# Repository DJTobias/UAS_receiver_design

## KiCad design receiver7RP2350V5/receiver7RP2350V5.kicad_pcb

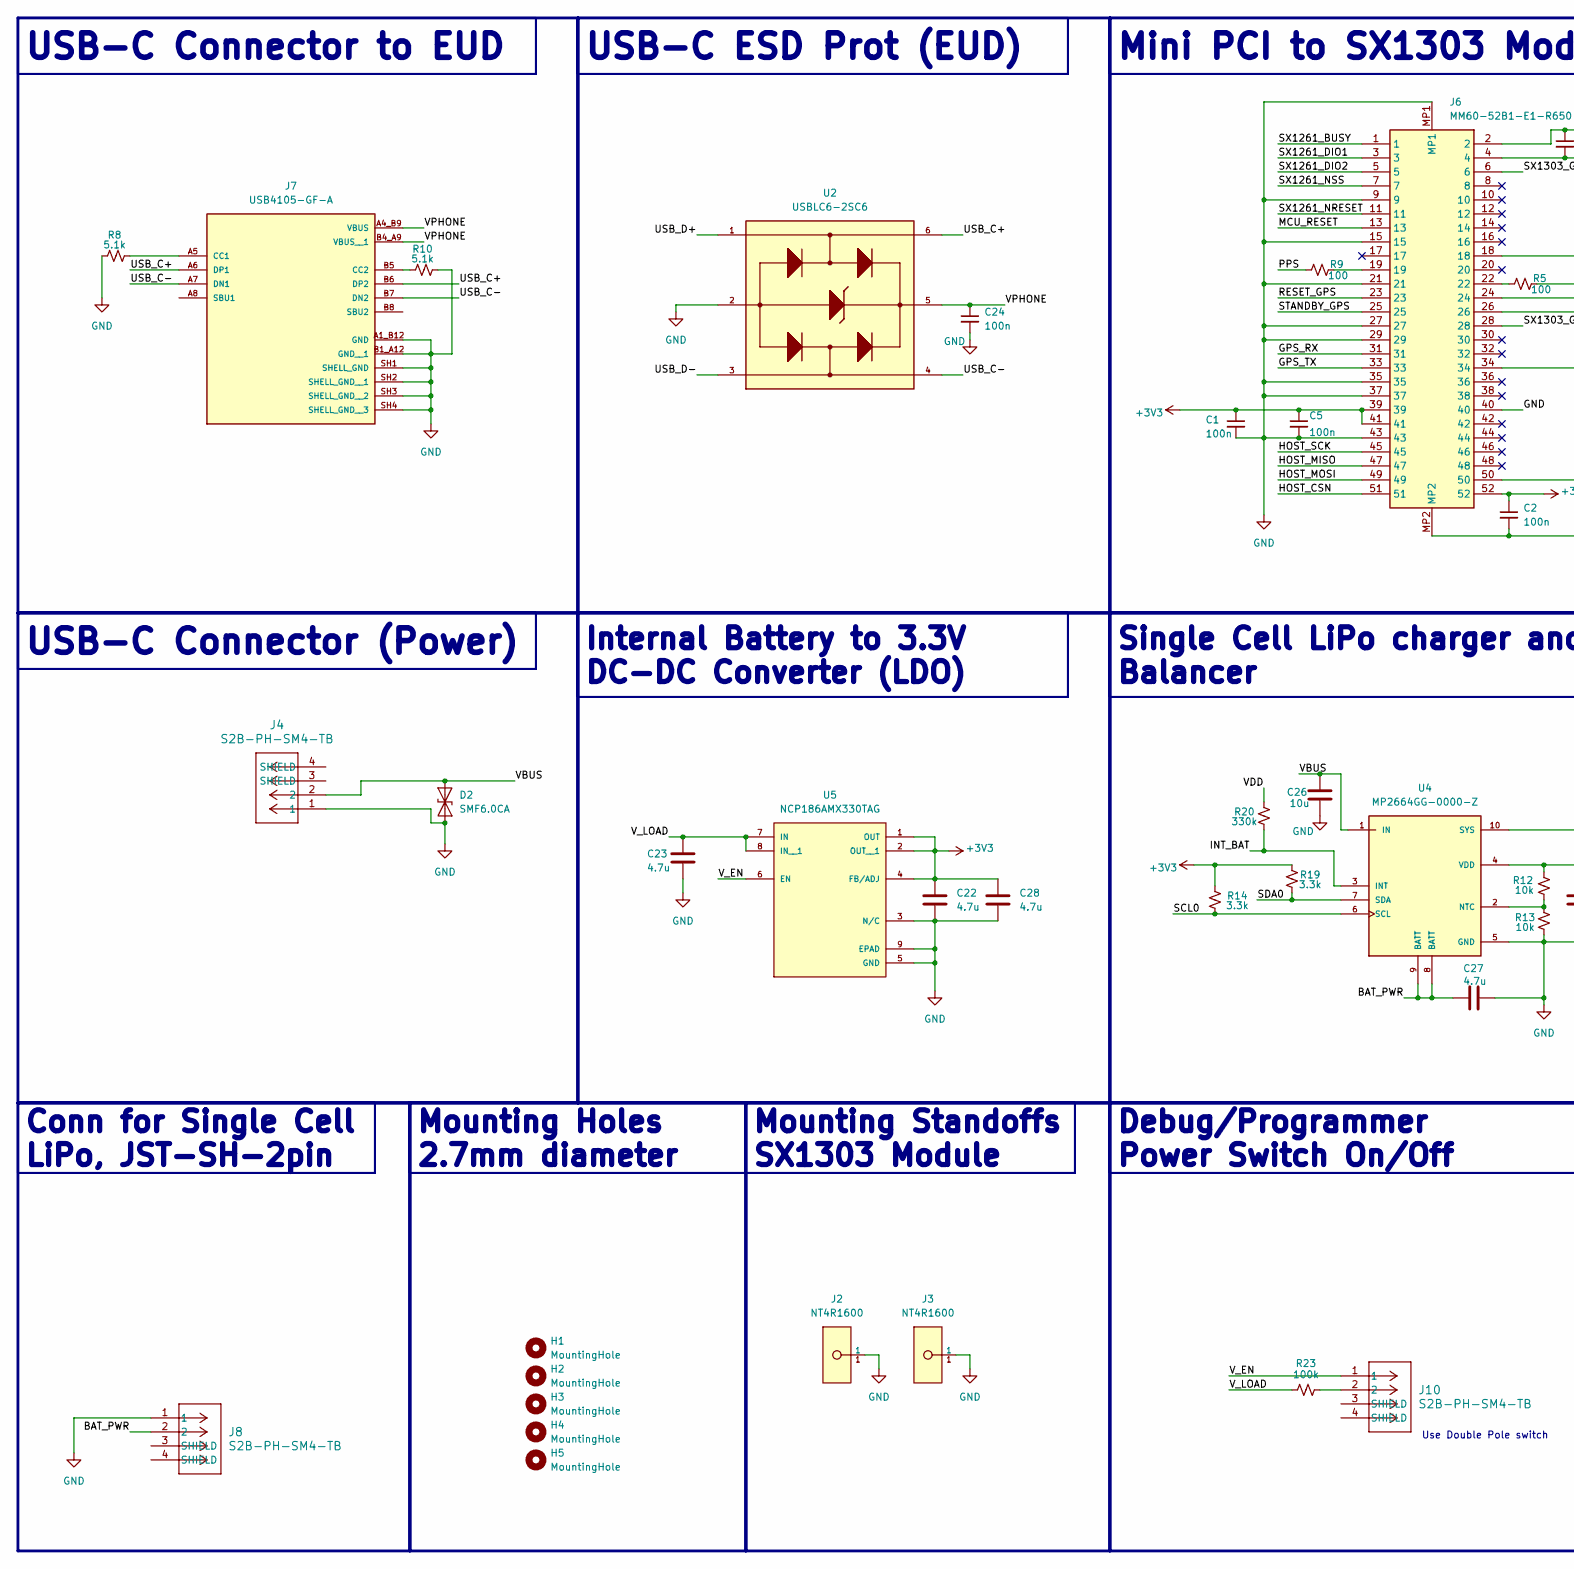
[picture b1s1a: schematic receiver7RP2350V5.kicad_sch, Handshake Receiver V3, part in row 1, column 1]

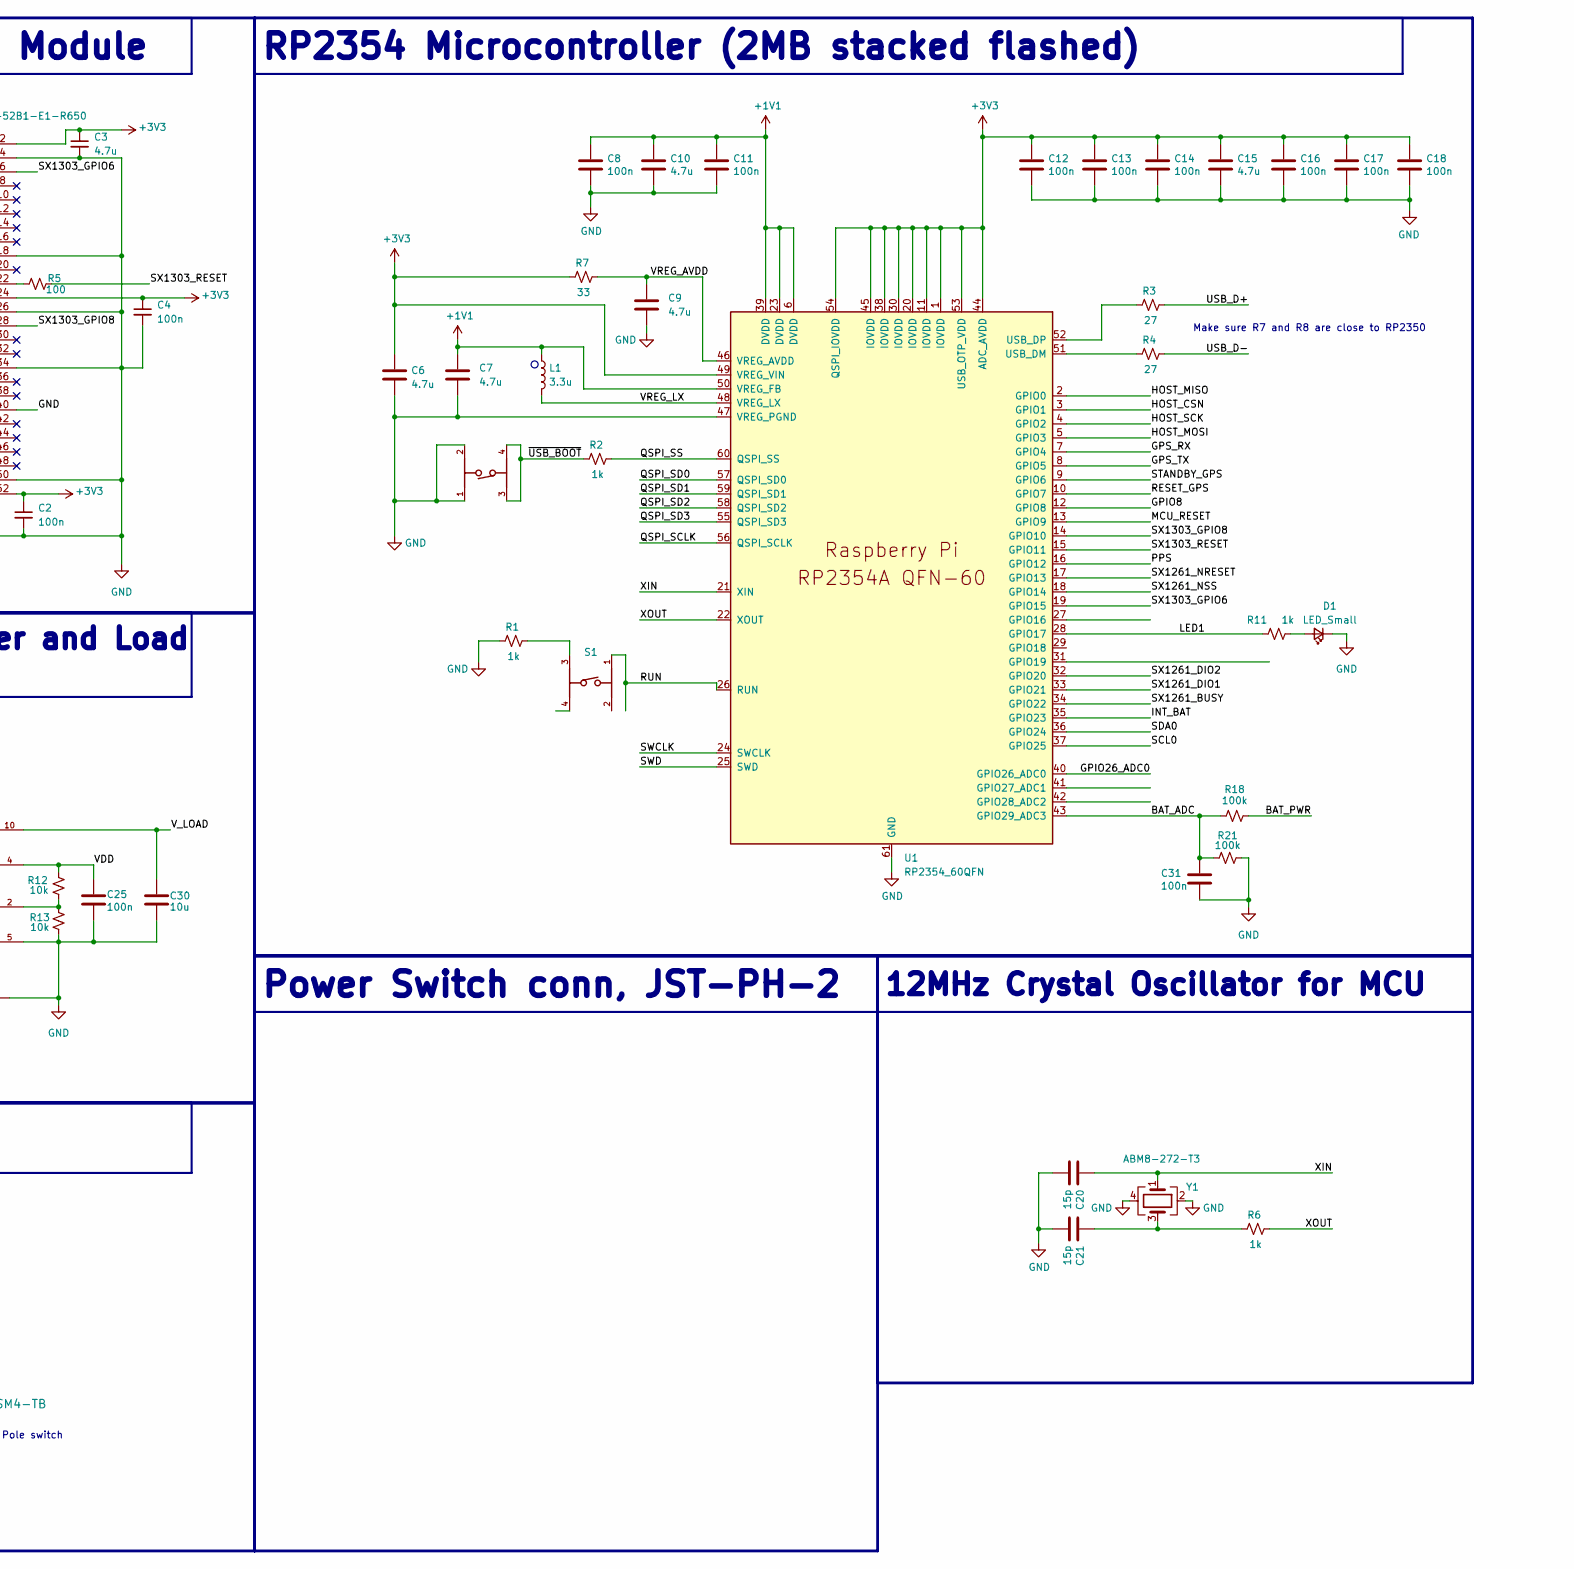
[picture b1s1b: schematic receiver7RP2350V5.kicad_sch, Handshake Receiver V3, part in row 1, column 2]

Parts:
C1, C2, C4, C5, C8, C11, C12, C13, C14, C16, C17, C18, C24, C25, C31: 100n; C_0402_1005Metric
C3, C9, C10, C15, C22, C23, C27, C28: 4.7u; C_0402_1005Metric
C6, C7: 4.7u; C_0402_1005Metric_small_pads
C20, C21: 15p; C_0402_1005Metric
C26, C30: 10u; C_0805_2012Metric
D1: LED_Small; LED_0402_1005Metric
D2: SMF6.0CA; SMF26CA_Custom
H1: MountingHole; MountingHole_2.5mm
H2, H3, H4, H5: MountingHole; MountingHole_2.7mm_M2.5_Pad_Via
J2, J3: NT4R1600; JAE_Electronics-NT4R1600-MFG; mouser part number 656-NT4R1600; digikey description STANDOFF FOR MM60 SERIES
J4, J8, J10: S2B-PH-SM4-TB; CONN_S2B-PH-SM4-TB_JST_mod2
J6: MM60-52B1-E1-R650; MM6052B1E1R650_mod_screw; Mouser Part Number 656-MM60-52B1-E1-R
J7: USB4105-GF-A; GCT_USB4105-GF-A; PARTREV B4
L1: 3.3u; L_pol_2016
R1, R2, R6, R11: 1k; R_0402_1005Metric
R3, R4: 27; R_0402_1005Metric
R5, R9: 100; R_0402_1005Metric
R7: 33; R_0402_1005Metric
R8, R10: 5.1k; R_0402_1005Metric
R12, R13: 10k; R_0402_1005Metric
R14, R19: 3.3k; R_0402_1005Metric
R18, R21, R23: 100k; R_0402_1005Metric
R20: 330k; R_0402_1005Metric
S1, S2: 434133025816; 434133025816_mod
U1: RP2354_60QFN; RP2350-QFN-60-1EP_7x7_P0.4mm_EP3.4x3.4mm_ThermalVias
U2: USBLC6-2SC6; SOT95P280X145-6N
U4: MP2664GG-0000-Z; QFN50P200X200X105-10N; PARTREV 1.01
U5: NCP186AMX330TAG; PSON40P160X120X45-9N; PARTREV Rev.5
Y1: ABM8-272-T3; Crystal_SMD_3225-4Pin_3.2x2.5mm

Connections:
+1V1: C7.1, C8.1, C10.1, C11.1, L1.1, U1.6 (DVDD), U1.23 (DVDD), U1.39 (DVDD), U1.50 (VREG_FB)
+3V3: C1.1, C2.1, C3.1, C4.1, C5.1, C6.1, C12.1, C13.1, C14.1, C15.1, C16.1, C17.1, C18.1, C22.1, C28.1, J6.2, J6.24, J6.39, J6.41, J6.52, R7.1, R14.2, R19.2, U1.1 (IOVDD), U1.11 (IOVDD), U1.20 (IOVDD), U1.30 (IOVDD), U1.38 (IOVDD), U1.44 (ADC_AVDD), U1.45 (IOVDD), U1.49 (VREG_VIN), U1.53 (USB_OTP_VDD), U1.54 (QSPI_IOVDD), U5.1 (OUT), U5.2 (OUT__1), U5.4 (FB/ADJ)
/BAT_ADC: C31.1, R18.2, R21.2, U1.43 (GPIO29_ADC3)
/BAT_PWR: C27.1, J8.2, R18.1, U4.8 (BATT), U4.9 (BATT)
/GPIO8: U1.12 (GPIO8)
/GPIO26_ADC0: U1.40 (GPIO26_ADC0)
/GPS_RX: J6.31, U1.7 (GPIO4)
/GPS_TX: J6.33, U1.8 (GPIO5)
/HOST_CSN: J6.51, U1.3 (GPIO1)
/HOST_MISO: J6.47, U1.2 (GPIO0)
/HOST_MOSI: J6.49, U1.5 (GPIO3)
/HOST_SCK: J6.45, U1.4 (GPIO2)
/INT_BAT: R20.1, U1.35 (GPIO23), U4.3 (INT)
/LED1: R11.1, U1.28 (GPIO17)
/MCU_RESET: J6.13, U1.13 (GPIO9)
/PPS: R9.1, U1.16 (GPIO12)
/QSPI_SCLK: U1.56 (QSPI_SCLK)
/QSPI_SD0: U1.57 (QSPI_SD0)
/QSPI_SD1: U1.59 (QSPI_SD1)
/QSPI_SD2: U1.58 (QSPI_SD2)
/QSPI_SD3: U1.55 (QSPI_SD3)
/QSPI_SS: R2.2, U1.60 (QSPI_SS)
/RESET_GPS: J6.23, U1.10 (GPIO7)
/RUN: S1.1, U1.26 (RUN)
/SCL0: R14.1, U1.37 (GPIO25), U4.6 (SCL)
/SDA0: R19.1, U1.36 (GPIO24), U4.7 (SDA)
/STANDBY_GPS: J6.25, U1.9 (GPIO6)
/SWCLK: U1.24 (SWCLK)
/SWD: U1.25 (SWD)
/SX1261_BUSY: J6.1, U1.34 (GPIO22)
/SX1261_DIO1: J6.3, U1.33 (GPIO21)
/SX1261_DIO2: J6.5, U1.32 (GPIO20)
/SX1261_NRESET: J6.11, U1.17 (GPIO13)
/SX1261_NSS: J6.7, U1.18 (GPIO14)
/SX1303_GPIO6: J6.6, U1.19 (GPIO15)
/SX1303_GPIO8: J6.28, U1.14 (GPIO10)
/SX1303_RESET: R5.2, U1.15 (GPIO11)
/USB_C+: J7.A6 (DP1), J7.B6 (DP2), U2.6
/USB_C-: J7.A7 (DN1), J7.B7 (DN2), U2.4
/USB_D+: R3.2, U2.1
/USB_D-: R4.2, U2.3
/VBUS: C26.1, D2.2 (A2), J4.2, U4.1 (IN)
/VDD: C25.1, R12.2, R20.2, U4.4 (VDD)
/VPHONE: C24.1, J7.A4_B9 (VBUS), J7.B4_A9 (VBUS__1), U2.5
/VREG_AVDD: C9.1, R7.2, U1.46 (VREG_AVDD)
/VREG_LX: L1.2, U1.48 (VREG_LX)
/V_EN: J10.1, U5.6 (EN)
/V_LOAD: C23.1, C30.1, R23.2, U4.10 (SYS), U5.7 (IN), U5.8 (IN__1)
/XIN: C20.1, U1.21 (XIN), Y1.1
/XOUT: R6.2, U1.22 (XOUT)
/~USB_BOOT: R2.1, S2.3, S2.4
GND: C1.2, C2.2, C3.2, C4.2, C5.2, C6.2, C7.2, C8.2, C9.2, C10.2, C11.2, C12.2, C13.2, C14.2, C15.2, C16.2, C17.2, C18.2, C20.2, C21.2, C22.2, C23.2, C24.2, C25.2, C26.2, C27.2, C28.2, C30.2, C31.2, D1.1 (K), D2.1 (A1), J2.1, J3.1, J4.1, J6.4, J6.9, J6.15, J6.18, J6.21, J6.26, J6.27, J6.29, J6.34, J6.35, J6.37, J6.40, J6.43, J6.50, J6.MP1, J6.MP2, J7.A1_B12 (GND), J7.B1_A12 (GND__1), J7.SH1 (SHELL_GND), J7.SH2 (SHELL_GND__1), J7.SH3 (SHELL_GND__2), J7.SH4 (SHELL_GND__3), J8.1, R1.1, R8.1, R10.2, R13.1, R21.1, S2.1, S2.2, U1.47 (VREG_PGND), U1.61 (GND), U2.2, U4.5 (GND), U5.3 (N/C), U5.5 (GND), U5.9 (EPAD), Y1.2, Y1.4
unnamed: C21.1, R6.1, Y1.3
unnamed: D1.2 (A), R11.2
unnamed: J6.19, R9.2
unnamed: J6.22, R5.1
unnamed: J7.A5 (CC1), R8.2
unnamed: J7.B5 (CC2), R10.1
unnamed: J10.2, R23.1
unnamed: R1.2, S1.3
unnamed: R4.1, U1.51 (USB_DM)
unnamed: R3.1, U1.52 (USB_DP)
unnamed: R12.1, R13.2, U4.2 (NTC)

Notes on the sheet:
Use Double Pole switch
Make sure R7 and R8 are close to RP2350
12MHz Crystal Oscillator for MCU
Debug/Programmer Power Switch On/Off
Conn for Single Cell LiPo, JST-SH-2pin
USB-C Connector (Power)
Power Switch conn, JST-PH-2
Mini PCI to SX1303 Module
USB-C ESD Prot (EUD)
Mounting Holes 2.7mm diameter
Single Cell LiPo charger and Load Balancer
Internal Battery to 3.3V DC-DC Converter (LDO)
Mounting Standoffs SX1303 Module
USB-C Connector to EUD
RP2354 Microcontroller (2MB stacked flashed)

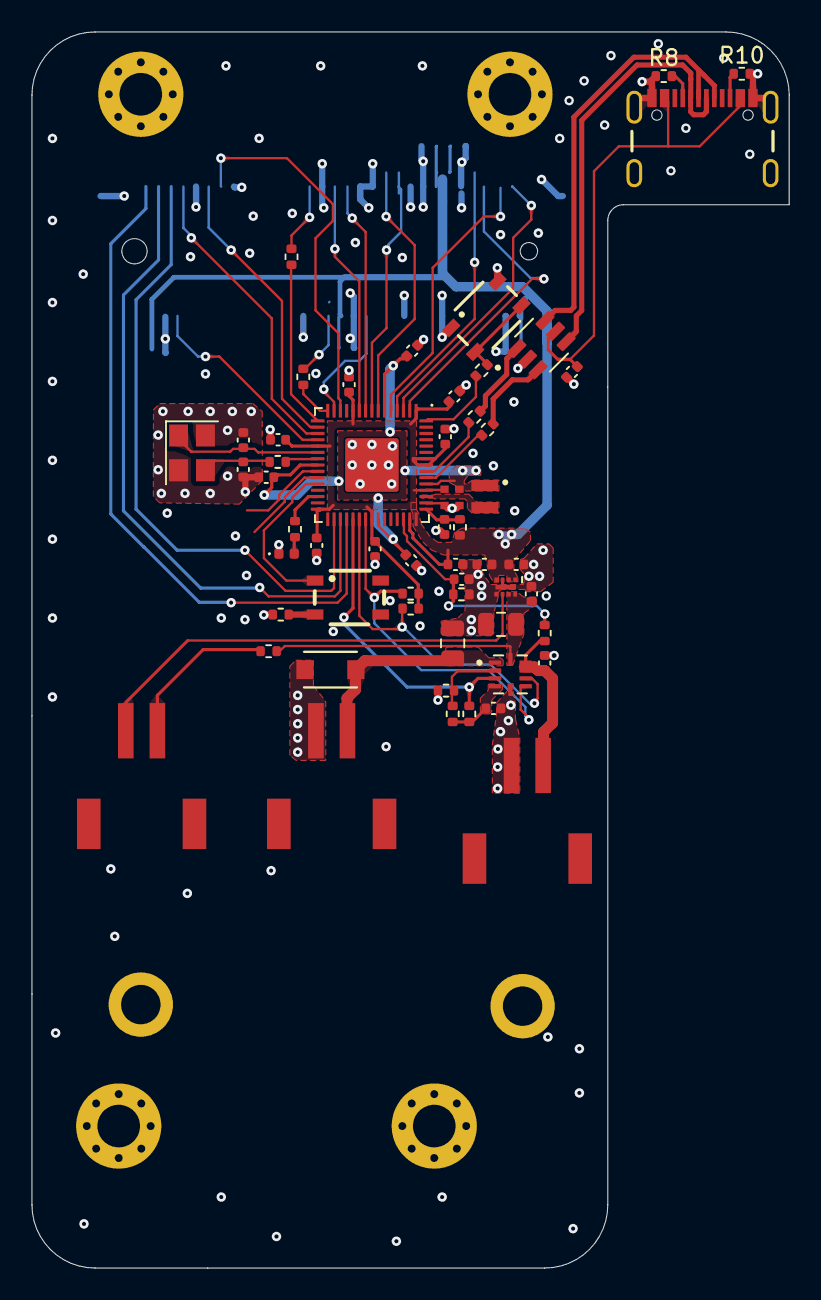
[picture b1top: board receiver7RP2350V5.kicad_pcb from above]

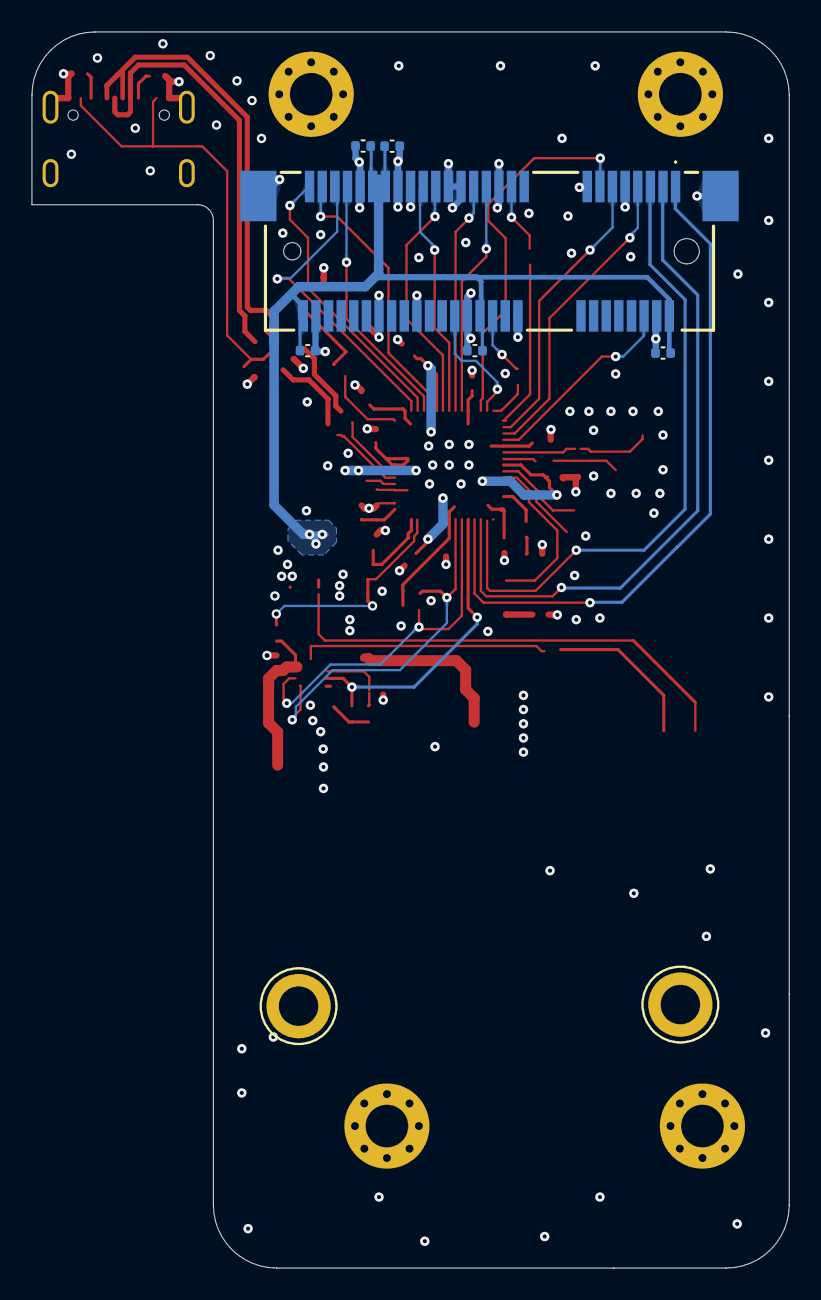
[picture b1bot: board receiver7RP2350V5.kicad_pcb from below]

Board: 4 copper layers, 48.0 x 78.3 mm, 70 parts (8 on the bottom side), 54 nets.

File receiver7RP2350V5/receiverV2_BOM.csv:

"Reference","Value","Datasheet","Footprint","Qty","DNP"
"C1,C2,C4,C5,C8,C11,C12,C13,C14,C16,C17,C18,C24,C25","100n","~","Capacitor_SMD:C_0402_1005Metric","14",""
"C3,C6,C7,C9,C10,C15,C27","4.7u","~","Capacitor_SMD:C_0402_1005Metric,RP2350_60QFN_minimal:C_0402_1005Metric_small_pads","7",""
"C19,C22,C23,C26,C30","10u","~","Capacitor_SMD:C_0805_2012Metric","5",""
"C20,C21","15p","~","Capacitor_SMD:C_0402_1005Metric","2",""
"D1","LED_Small","~","LED_SMD:LED_0402_1005Metric","1",""
"J1","BM04B-SRSS-TB","BM04B-SRSS-TB","BM04B_SRSS_TB:CONN4_BM04B-SRSS_JST","1",""
"J2,J3","NT4R1600","https://www.jae.com/en/connectors/series/detail/product/id=68912","NT4R1600:JAE_Electronics-NT4R1600-MFG","2",""
"J4","2pads","S3B-PH-SM4-TB","PADS:2pin pad_larger","1",""
"J6","MM60-52B1-E1-R650","https://www.mouser.in/datasheet/2/206/JAEIS03536_1-2550299.pdf","MM60-52B1-E1-R650:MM6052B1E1R650_mod_screw","1",""
"J7","USB4105-GF-A","","USB4105_GF_A:GCT_USB4105-GF-A","1",""
"J8,J10","S2B-PH-SM4-TB","S2B-PH-SM4-TB","JST2pin:CONN_S2B-PH-SM4-TB_JST_mod2","2",""
"L1","3.3u","~","RP2350_60QFN_minimal:L_pol_2016","1",""
"R1,R2,R6,R11","1k","~","Resistor_SMD:R_0402_1005Metric","4",""
"R3,R4","27","~","Resistor_SMD:R_0402_1005Metric","2",""
"R5,R9","100","~","Resistor_SMD:R_0402_1005Metric","2",""
"R7","33","~","Resistor_SMD:R_0402_1005Metric","1",""
"R8,R10","5.1k","~","Resistor_SMD:R_0402_1005Metric","2",""
"R12,R13","10k","~","Resistor_SMD:R_0402_1005Metric","2",""
"R14,R19","3.3k","~","Resistor_SMD:R_0402_1005Metric","2",""
"R15","100k","~","Resistor_SMD:R_0402_1005Metric","1",""
"R20","300k","~","Resistor_SMD:R_0402_1005Metric","1",""
"S1","434133025816","","434133025816:434133025816_mod","1",""
"U1","RP2350_60QFN","","RP2350_60QFN_minimal:RP2350-QFN-60-1EP_7x7_P0.4mm_EP3.4x3.4mm_ThermalVias","1",""
"U2","USBLC6-2SC6","","USBLC6_2SC6:SOT95P280X145-6N","1",""
"U3","AP7361C-33Y5-13","AP7361C-33Y5-13","AP7361C_33Y5_13:SOT89-5_DIO-M_MODGND","1",""
"U4","MP2664GG-0000-Z","","MP2664GG-0000-Z:QFN50P200X200X105-10N","1",""
"Y1","ABM8-272-T3","~","adafruit:Crystal_SMD_3225-4Pin_3.2x2.5mm","1",""

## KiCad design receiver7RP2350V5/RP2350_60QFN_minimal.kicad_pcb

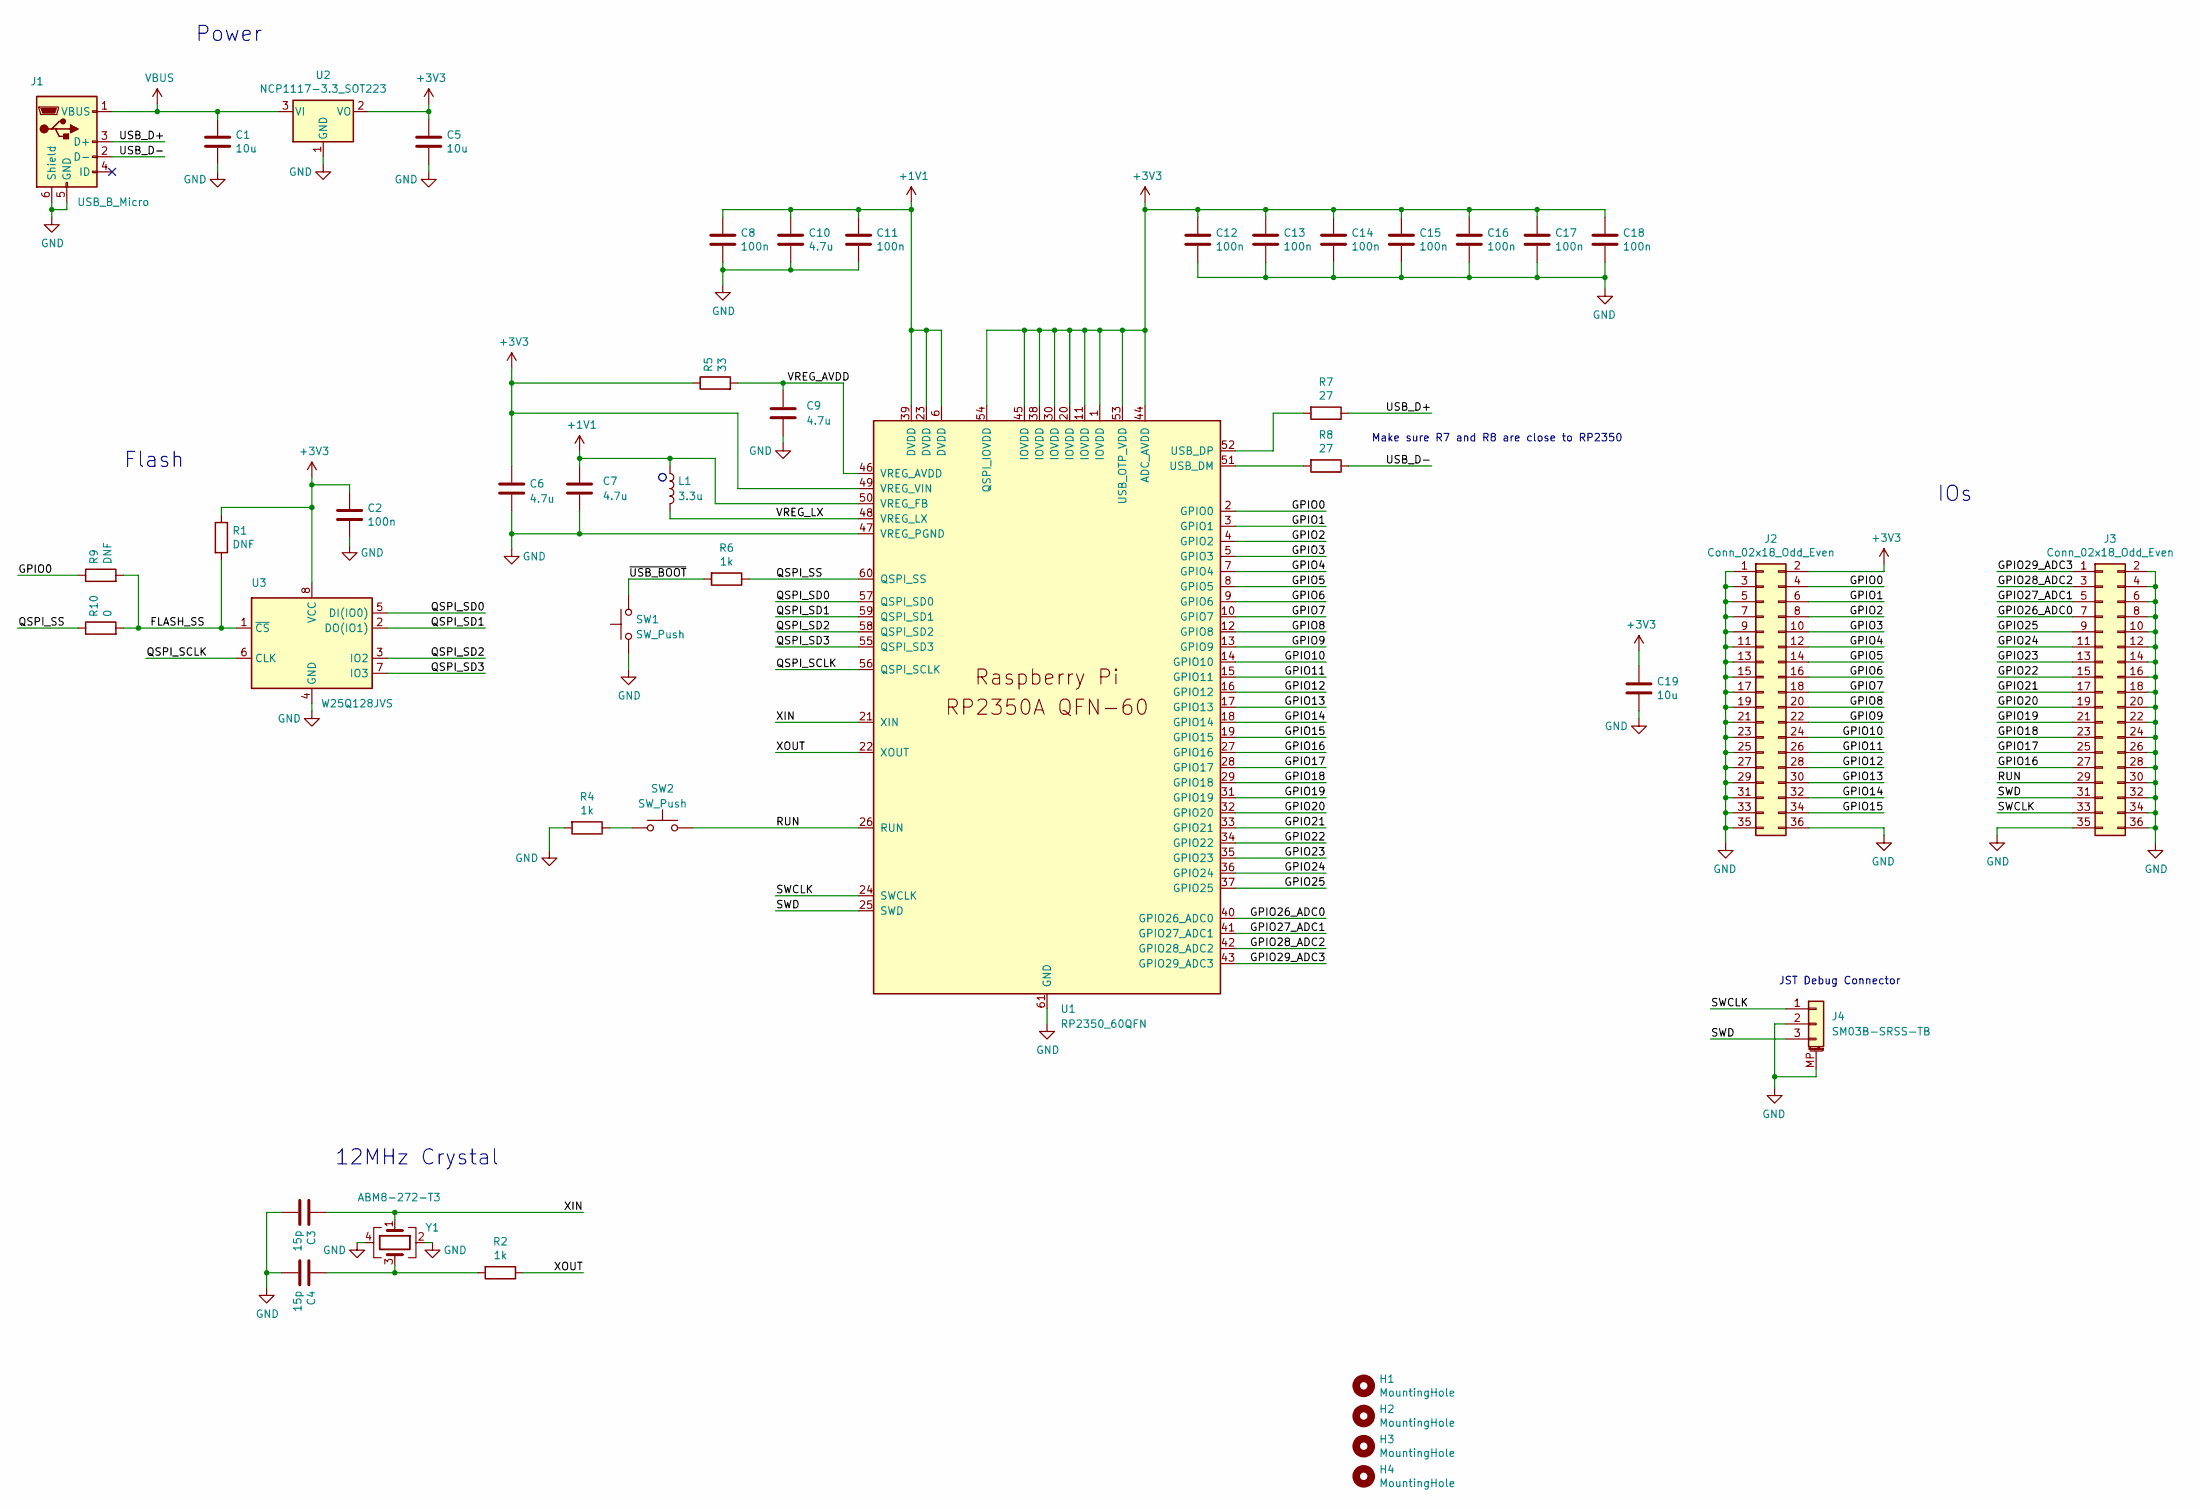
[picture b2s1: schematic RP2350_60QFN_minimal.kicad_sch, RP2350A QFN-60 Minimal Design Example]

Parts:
C1, C5, C19: 10u; C_0805_2012Metric
C2, C8, C11, C12, C13, C14, C15, C16, C17, C18: 100n; C_0402_1005Metric
C3, C4: 15p; C_0402_1005Metric
C6, C7: 4.7u; C_0402_1005Metric_small_pads
C9, C10: 4.7u; C_0402_1005Metric
H1, H2, H3, H4: MountingHole; MountingHole_2.7mm_M2.5
J1: USB_B_Micro; USB_Micro-B_Amphenol_10103594-0001LF_Horizontal
J2, J3: Conn_02x18_Odd_Even; PinHeader_2x18_P2.54mm_Vertical
J4: SM03B-SRSS-TB; JST_SH_SM03B-SRSS-TB_1x03-1MP_P1.00mm_Horizontal
L1: 3.3u; L_pol_2016
R1, R9: DNF; R_0402_1005Metric
R2, R4, R6: 1k; R_0402_1005Metric
R5: 33; R_0402_1005Metric
R7, R8: 27; R_0402_1005Metric
R10: 0; R_0402_1005Metric
SW1, SW2: SW_Push; SW_Push_1P1T_NO_Vertical_Wuerth_434133025816
U1: RP2350_60QFN; RP2350-QFN-60-1EP_7x7_P0.4mm_EP3.4x3.4mm_ThermalVias
U2: NCP1117-3.3_SOT223; SOT-223-3_TabPin2
U3: W25Q128JVS; SOIC-8_5.23x5.23mm_P1.27mm
Y1: ABM8-272-T3; Crystal_SMD_3225-4Pin_3.2x2.5mm

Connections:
+1V1: C7.1, C8.1, C10.1, C11.1, L1.1, U1.6 (DVDD), U1.23 (DVDD), U1.39 (DVDD), U1.50 (VREG_FB)
+3V3: C2.1, C5.1, C6.1, C12.1, C13.1, C14.1, C15.1, C16.1, C17.1, C18.1, C19.1, J2.2, R1.1, R5.1, U1.1 (IOVDD), U1.11 (IOVDD), U1.20 (IOVDD), U1.30 (IOVDD), U1.38 (IOVDD), U1.44 (ADC_AVDD), U1.45 (IOVDD), U1.49 (VREG_VIN), U1.53 (USB_OTP_VDD), U1.54 (QSPI_IOVDD), U2.2 (VO), U3.8 (VCC)
/FLASH_SS: R1.2, R9.2, R10.2, U3.1 (~CS)
/GPIO0: J2.4, R9.1, U1.2 (GPIO0)
/GPIO1: J2.6, U1.3 (GPIO1)
/GPIO2: J2.8, U1.4 (GPIO2)
/GPIO3: J2.10, U1.5 (GPIO3)
/GPIO4: J2.12, U1.7 (GPIO4)
/GPIO5: J2.14, U1.8 (GPIO5)
/GPIO6: J2.16, U1.9 (GPIO6)
/GPIO7: J2.18, U1.10 (GPIO7)
/GPIO8: J2.20, U1.12 (GPIO8)
/GPIO9: J2.22, U1.13 (GPIO9)
/GPIO10: J2.24, U1.14 (GPIO10)
/GPIO11: J2.26, U1.15 (GPIO11)
/GPIO12: J2.28, U1.16 (GPIO12)
/GPIO13: J2.30, U1.17 (GPIO13)
/GPIO14: J2.32, U1.18 (GPIO14)
/GPIO15: J2.34, U1.19 (GPIO15)
/GPIO16: J3.27, U1.27 (GPIO16)
/GPIO17: J3.25, U1.28 (GPIO17)
/GPIO18: J3.23, U1.29 (GPIO18)
/GPIO19: J3.21, U1.31 (GPIO19)
/GPIO20: J3.19, U1.32 (GPIO20)
/GPIO21: J3.17, U1.33 (GPIO21)
/GPIO22: J3.15, U1.34 (GPIO22)
/GPIO23: J3.13, U1.35 (GPIO23)
/GPIO24: J3.11, U1.36 (GPIO24)
/GPIO25: J3.9, U1.37 (GPIO25)
/GPIO26_ADC0: J3.7, U1.40 (GPIO26_ADC0)
/GPIO27_ADC1: J3.5, U1.41 (GPIO27_ADC1)
/GPIO28_ADC2: J3.3, U1.42 (GPIO28_ADC2)
/GPIO29_ADC3: J3.1, U1.43 (GPIO29_ADC3)
/QSPI_SCLK: U1.56 (QSPI_SCLK), U3.6 (CLK)
/QSPI_SD0: U1.57 (QSPI_SD0), U3.5 (DI(IO0))
/QSPI_SD1: U1.59 (QSPI_SD1), U3.2 (DO(IO1))
/QSPI_SD2: U1.58 (QSPI_SD2), U3.3 (IO2)
/QSPI_SD3: U1.55 (QSPI_SD3), U3.7 (IO3)
/QSPI_SS: R6.1, R10.1, U1.60 (QSPI_SS)
/RUN: J3.29, SW2.2, U1.26 (RUN)
/SWCLK: J3.33, J4.1, U1.24 (SWCLK)
/SWD: J3.31, J4.3, U1.25 (SWD)
/USB_D+: J1.3 (D+), R7.1
/USB_D-: J1.2 (D-), R8.1
/VREG_AVDD: C9.1, R5.2, U1.46 (VREG_AVDD)
/VREG_LX: L1.2, U1.48 (VREG_LX)
/XIN: C3.1, U1.21 (XIN), Y1.1
/XOUT: R2.1, U1.22 (XOUT)
/~USB_BOOT: R6.2, SW1.2
GND: C1.2, C2.2, C3.2, C4.2, C5.2, C6.2, C7.2, C8.2, C9.2, C10.2, C11.2, C12.2, C13.2, C14.2, C15.2, C16.2, C17.2, C18.2, C19.2, J1.5 (GND), J1.6 (Shield), J2.1, J2.3, J2.5, J2.7, J2.9, J2.11, J2.13, J2.15, J2.17, J2.19, J2.21, J2.23, J2.25, J2.27, J2.29, J2.31, J2.33, J2.35, J2.36, J3.2, J3.4, J3.6, J3.8, J3.10, J3.12, J3.14, J3.16, J3.18, J3.20, J3.22, J3.24, J3.26, J3.28, J3.30, J3.32, J3.34, J3.35, J3.36, J4.2, J4.MP (MountPin), R4.2, SW1.1, U1.47 (VREG_PGND), U1.61 (GND), U2.1 (GND), U3.4 (GND), Y1.2, Y1.4
unnamed: C4.1, R2.2, Y1.3
unnamed: R4.1, SW2.1
unnamed: R8.2, U1.51 (USB_DM)
unnamed: R7.2, U1.52 (USB_DP)
VBUS: C1.1, J1.1 (VBUS), U2.3 (VI)

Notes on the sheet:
JST Debug Connector
IOs
Flash
Make sure R7 and R8 are close to RP2350
12MHz Crystal
Power

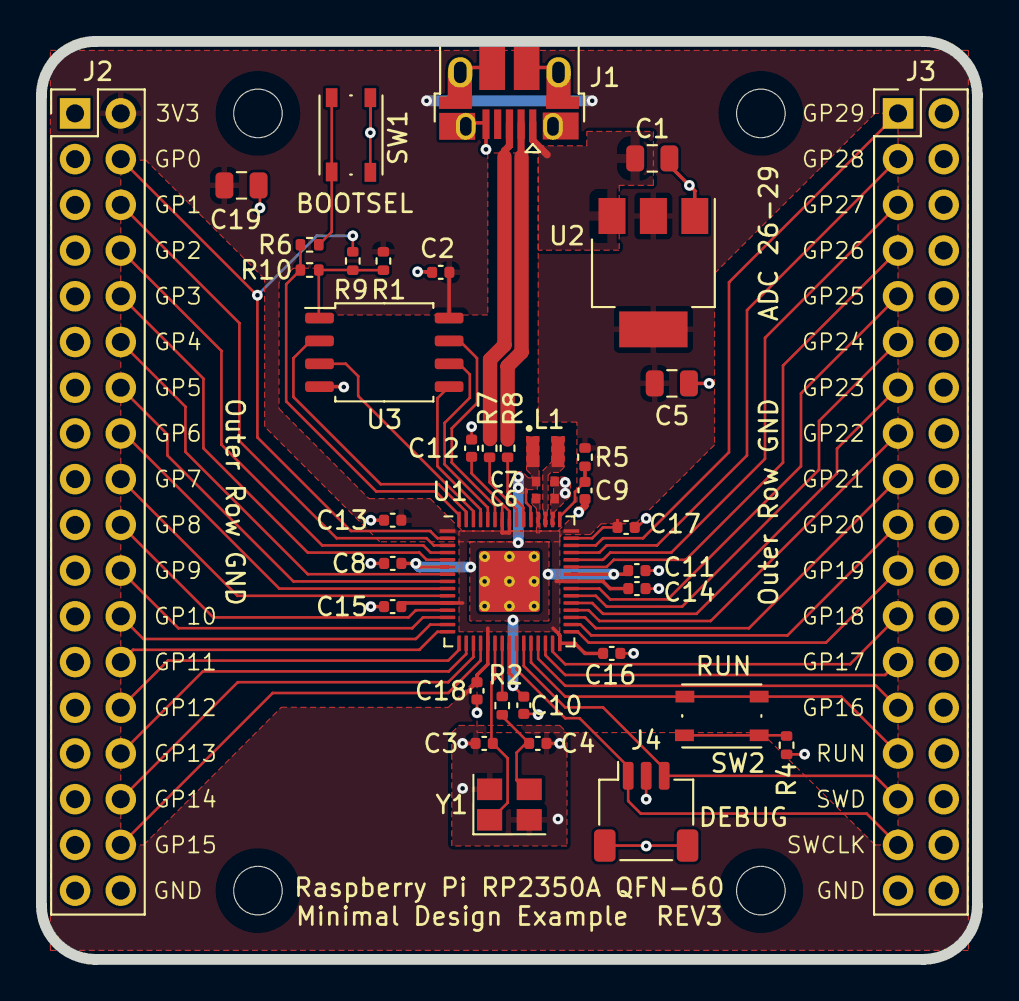
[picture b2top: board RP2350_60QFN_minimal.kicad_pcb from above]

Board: 2 copper layers, 52.0 x 51.0 mm, 43 parts (0 on the bottom side), 55 nets.

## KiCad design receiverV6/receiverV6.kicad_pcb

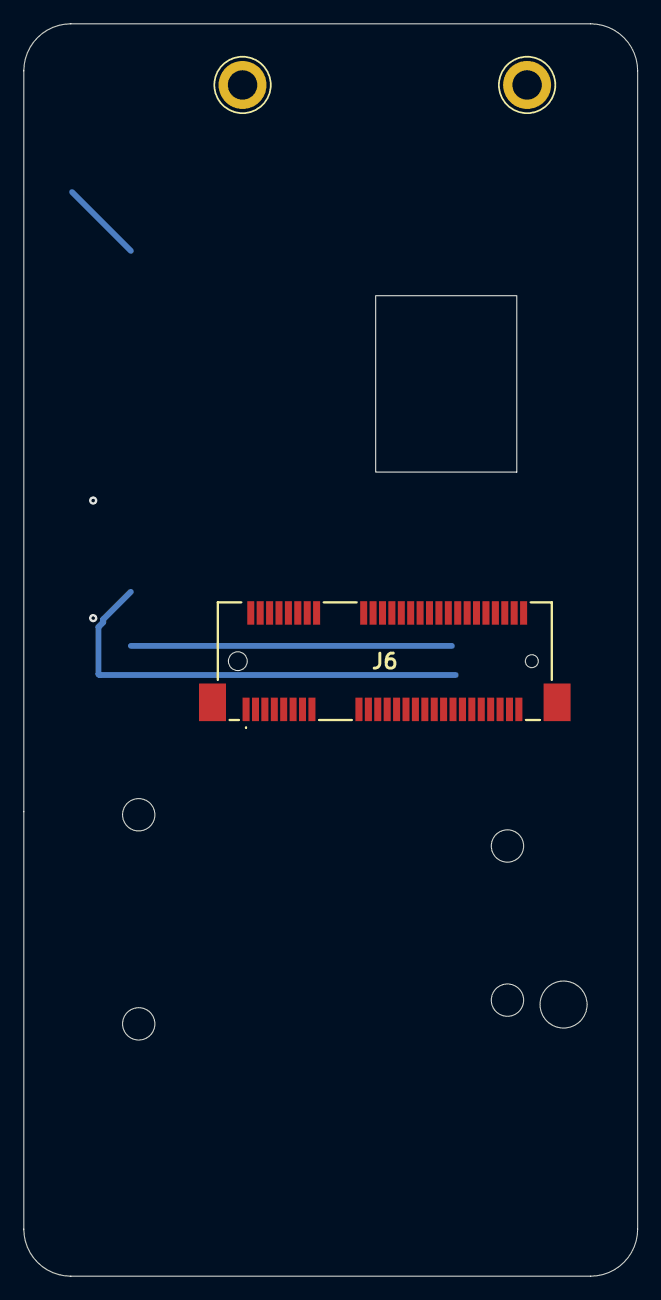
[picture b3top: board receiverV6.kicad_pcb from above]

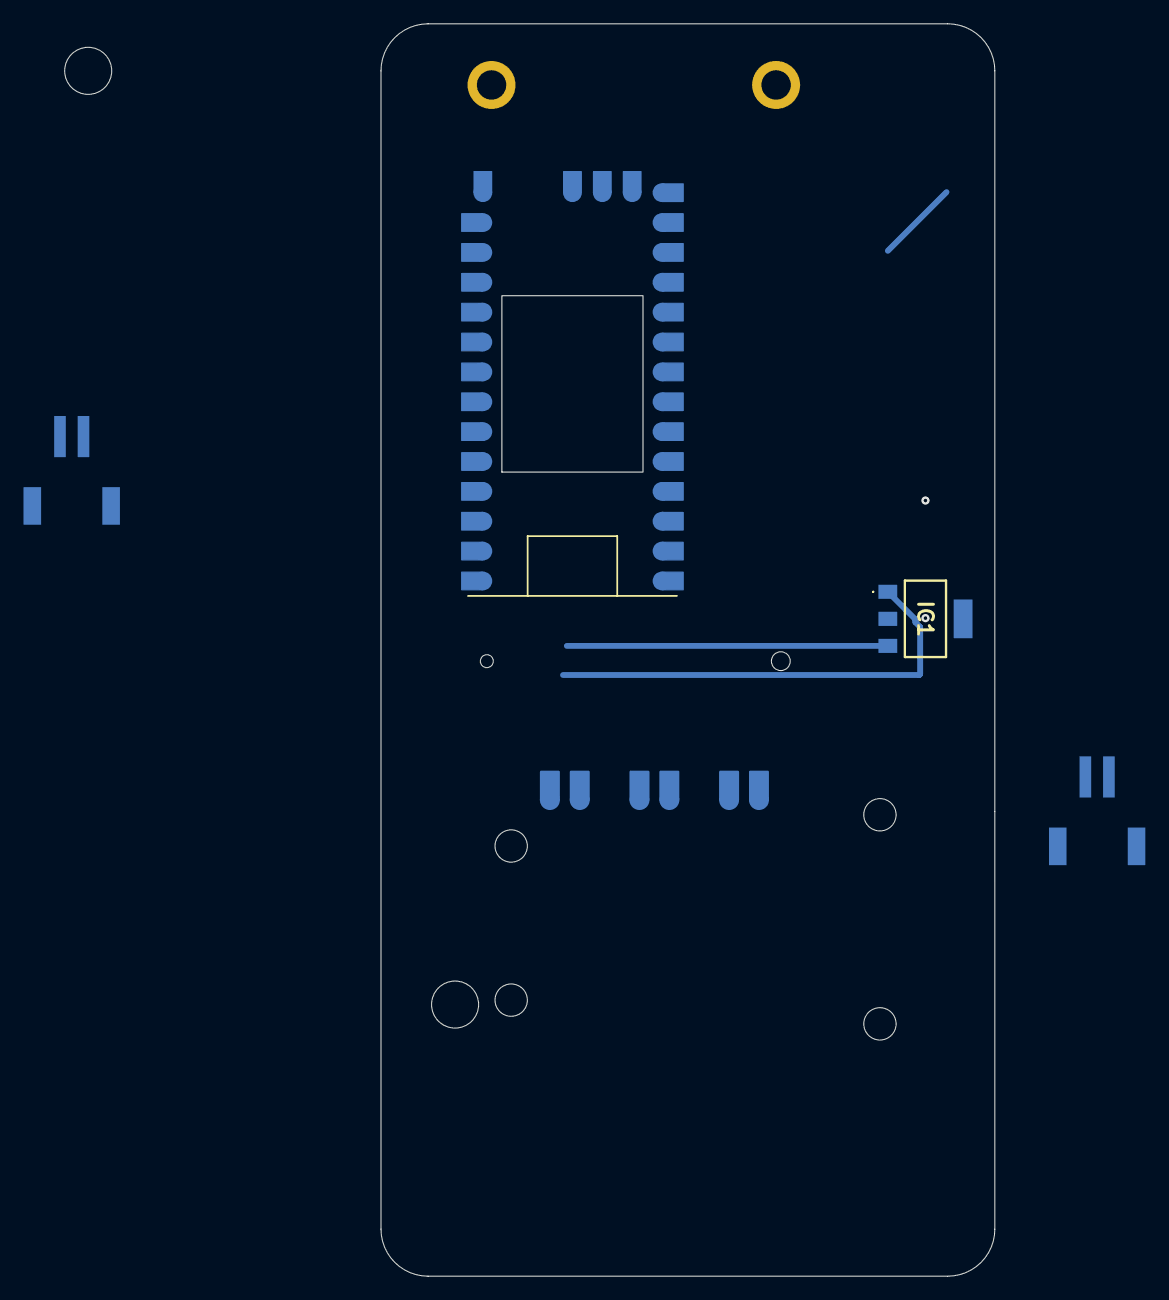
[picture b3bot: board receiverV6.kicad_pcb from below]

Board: 4 copper layers, 52.2 x 106.5 mm, 10 parts (5 on the bottom side), 9 nets.

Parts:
H5, H6, H7, H8: MountingHole; MountingHole_4mm_t4
IC1: AP7361C-33E-13; AP7361C33E13
J2: adafruitpwr1000; adafruit powerboost 1000 5pinpads
J3, J4: S2B-PH-SM4-TB; CONN_S2B-PH-SM4-TB_JST_mod2
J6: MM60-52B1-E1-R650; MM6052B1E1R650
U1: Teensy4.0; Teensy40_smd_mod_receiver

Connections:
+3.3V: IC1.3 (OUT), J6.2, J6.24, J6.39, J6.41, J6.52
+5V: IC1.1 (IN), J2.8 (5V)
/HOST_CSN: J6.51, U1.12 (10_CS_MQSR)
/HOST_MISO: J6.47, U1.14 (12_MISO_MQSL)
/HOST_MOSI: J6.49, U1.13 (11_MOSI_CTX1)
/HOST_SCK: J6.45, U1.20 (13_SCK_CRX1_LED)
/SX1261_NRESET: J6.11, J6.13
/VBUS: J2.1 (USB_PWR), J3.2
GND: J2.5 (GND), J2.7 (GND), J3.1, J4.1, J6.4, J6.9, J6.15, J6.18, J6.21, J6.26, J6.27, J6.29, J6.34, J6.35, J6.37, J6.40, J6.43, J6.50, J6.MP1, J6.MP2
